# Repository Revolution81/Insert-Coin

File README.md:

<h1 align="center">Insert Coin</h1>

<p align="center">
  <b>A Bitcoin wallet for the M5Stack Cardputer Zero, with a 16-bit arcade look.</b><br>
  Starts with every radio off. Only the signer, in its own locked-down process, ever touches your keys.
</p>

<p align="center">
  <a href="docs/Insert-Coin-Instruction-Booklet.pdf">Instruction booklet (PDF)</a> ·
  <a href="SECURITY.md">Security model</a> ·
  <a href="docs/AUDIT.md">Security review</a> ·
  <a href="CHANGELOG.md">Changelog</a> ·
  <a href="LICENSE">License</a> ·
  <a href="docs/HARDWARE_TEST.md">Hardware test plan</a> ·
  <a href="#donate">Donate</a>
</p>

> [!WARNING]
> Insert Coin is new and **has not had an outside security audit**. The same
> person who wrote it reviewed it. Use testnet or signet first, and keep only
> small amounts on it until it has been reviewed independently.

---

It boots to an animated INSERT COIN title screen (the bitcoin is the O, and
"Running bitcoin..." is a nod to Hal Finney's first tweet about Bitcoin), and
OK plays an original chiptune fanfare. Then it's a full wallet: send, receive,
coin control, multisig, inheritance, tap cards, paper wallets, all on the
Cardputer's own screen and keys.

| | | | |
|:-:|:-:|:-:|:-:|
|  |  |  |  |
| **Home** | **Receive** | **Verify on the signer** | **Confirm send** |
|  |  |  |  |
| **Setup** | **Spending policy** | **Login countdown** | **Print a paper wallet** |

## Features

**Two modes.** Vault mode (the boot default) has Wi-Fi, Bluetooth and
Ethernet (LAN) switched off: sign PSBTs by animated QR or microSD with Sparrow or
any watch-only wallet. Online mode talks to your own Electrum server, through
Tor by default, and sends straight from the device, limited by a daily
online cap.

**Simple by default.** SETUP › DEVICE › ADVANCED (off out of the box) shows the
power-user tools: Co-Sign, temporary seed, child seeds, Key Teleport,
address explorer, paper wallets, watch-only and label exports, QR format,
and the Taproot choice for new multisig. Off, the menus keep to the
everyday things; a tool that's in use stays visible either way.

**Wallet**
- BIP39 seeds (12, 18 or 24 words) or a master xprv. New seeds mix the kernel RNG, the secure chip
  if fitted, and any dice rolls, coin flips, card shuffles or key mashing you add
- Native SegWit (BIP84) and Taproot (BIP86), several accounts per seed, optional passphrase
- Coin control, labels, fee bumps and cancels (RBF), CSV history export
- Pay silent payment addresses (BIP-352) and PayJoin requests (BIP-78)
- Multisig cosigner (BIP48, SegWit or Taproot), inheritance wallets with a time-locked heir key,
  and any miniscript wallet (Liana, Coldcard, Bitcoin Core) with this device's key
- Child seeds and passwords (BIP85), message signing (BIP137, BIP322)
- Temporary seeds and a Seed Vault of extra seeds; an address explorer
- Key Teleport (COLDCARD-compatible): seeds, notes and PSBTs to another device by QR
- Co-Sign: a 2-of-3 where a second key on the device signs only inside its own rules
- QR in every format that matters: PSBT, UR, BBQr, SeedQR
- SATSCARD and TAPSIGNER over NFC (M5Stack's Cap CC1101 & NFC on top, or the NFC Unit on the side port)

**Backups**: seed words, SeedQR, SLIP39 split shares, Seed XOR, and an encrypted card
backup of accounts, multisig wallets, labels, notes, the seed vault and settings
(not your seed itself), with a check that it opens.

**Notes & passwords** kept by the signer, encrypted with the seed.

**Guards**, all on the signer and all changed only with your PIN:
- **Spending policy**: per payment, per day, cooldown, address allow-list, max fee rate
- **Phone 2FA** (TOTP) for every payment or only big ones
- **Bypass PIN** that locks the policy, so your PIN alone can't loosen it or export the seed
- **Login countdown**: a wait of 5 minutes to 24 hours after the right PIN
- **Wipe PIN** (erases everything, device starts like new) and **duress PIN** (opens a decoy wallet)
- **Game PIN**: opens COIN INVADERS, a little space shooter, instead of the wallet, so the
  device looks like a toy (say, at a border). GAME ONLY leaves the wallet locked underneath;
  GAME + WIPE erases everything first. Hold HOME to leave the game
- **Auto lock** after 2 to 15 minutes, a custom time, or never
- Ten wrong PINs erase the wallet; every kind of PIN costs the same time to check

**Extras**: paper wallets kept off the microSD card, printed at home over
encrypted IPP (any AirPrint or IPP Everywhere printer) with a pinned printer certificate, or downloaded with SHARE
FILES (password-protected, local network only, switches itself off), or
SAVE TO USB STICK for your history and PSBTs. Optional
secure chip and fingerprint sensor. One sound switch for the menu boop and
the title fanfare.

## How it's put together

Separate processes, each its own Linux user, so a bug in one doesn't hand
over the others:

| Process | Holds | Network |
|---|---|---|
| **czsigner** | the seed, while unlocked; the screen and keyboard | none |
| **czapp** (the wallet you see) | public keys, history, labels | none |
| **cznet** | nothing | Tor and your Electrum server only |
| **czscan** | nothing; sees the camera | none |
| **czshare** | history exports and paper wallets, while sharing | local network only |
| **czprint** | paper wallets, while printing | local printers only |

The signer doesn't trust the app. It draws its own screens (gold shield in
the corner, your two security words on PIN screens), asks for your PIN and
your YES itself, re-reads every PSBT, re-derives every input and change
output from the seed, needs full previous transactions for SegWit v0 inputs,
checks your spending rules, and signs only the exact PSBT you confirmed.
[SECURITY.md](SECURITY.md) goes through what each process is trusted with
and what's known to be weak.

## Try it on your PC (simulator)

```
pip install -r requirements.txt pygame
python3 sim.py
```

The real app in a window at 3x size. It runs on **signet** (mainnet is off,
because a seed typed into a PC is hot) and simulates Vault/Online without
touching your network settings. Keys follow the Cardputer layout: Enter = OK,
Backspace = DEL, Esc = HOME, F Z X C or the arrow keys move. F12 saves a
screenshot. Data lives in `./simdata`; delete it to start over.

On Windows, put paths with spaces in quotes: `cd "C:\Users\you\Insert Coin"`.

## Install on the Cardputer Zero

Insert Coin comes in two editions. **Pick by how much money it will hold.**

| | **Savings edition** | **Spending edition** |
|---|---|---|
| What it is | A wallet image: the device boots into Insert Coin and runs nothing else | An app in M5Stack's launcher, next to your other apps |
| For | Savings, real amounts | Spending money only, like cash in a pocket |
| Other apps on the device | None | Anything you install from M5Stack's store, which could reach the wallet while it's open |
| How it's labelled | **SAVINGS WALLET** on the title screen, *Savings* in the file name | **SPENDING WALLET** on the title screen, *Insert Coin Spending* in the launcher |

The wallet inside is the same: the signer in its own locked-down process,
Vault mode at every start, your PIN and spending rules. The difference is
what else shares the device. [SECURITY.md](SECURITY.md#app-mode) has the
details.

### Savings edition

**Wallet image (recommended).** Burn
`Insert-Coin-Savings-<version>-cardputerzero.img.xz` from the releases page
with M5 Imager or Raspberry Pi Imager (*Use custom*), after checking its
SHA-256. It's M5Stack's CardputerZero OS with Insert Coin installed in
dedicated mode by `tools/build_image.sh`, built in public by the *Build
wallet image* workflow, so anyone can see what went in. It fits an 8 GB card
or bigger. It takes **no logins at all**: SSH is off and every account's
password is locked, so the screen and keyboard are the only way in. Browsers,
media players and remote-desktop servers are removed from it.

**Updating.** Releases that only change the wallet come as two files,
`Insert-Coin-Update-<version>.tar.gz` and its `.sig`. Put the card in a PC,
copy both into a folder named `Insert-Coin-Update` on its boot partition (or
onto a USB stick), put the card back and open SETUP › UPDATE. The wallet checks the
signature against the release key built into the image, shows the version
and SHA-256, and installs; the previous version is kept. Releases that need a
newer M5Stack OS come as a new image instead: have your seed words, copy the
card's `czwallet-backup` folder off first, burn, restore from words, and the
wallet offers to bring back your accounts and settings.

*If the image won't start:* put the card in a PC, create an empty file named
`insert-coin-debug.txt` on its boot partition (the part Windows can read),
put it back and power on for 10 minutes. The device then writes its startup
log to `insert-coin-bootlog.txt` on the same partition. Delete both files
afterwards: the log can name your Wi-Fi network.

**Or on the card you already have:** `sudo sh deploy/install.sh --dedicated`,
then `sudo reboot`. `sudo sh deploy/uninstall.sh` brings the launcher back.

### Spending edition

Keeps the CardputerZero home screen; **Insert Coin Spending** gets an icon
there. Over SSH:
```
sudo apt-get install -y git
git clone https://github.com/Revolution81/Insert-Coin.git
cd Insert-Coin && sudo sh deploy/install.sh --app
```
Opening the icon starts the wallet in Vault mode; SETUP › EXIT TO MENU locks
it, stops every wallet service and puts Wi-Fi back as it was.
To update: `cd ~/Insert-Coin && git pull && sudo sh deploy/install.sh --app`
(quick after the first time: steps already done are skipped).
`sudo sh deploy/uninstall.sh` removes it. Keep only spending money on it.

The installer creates the service users, installs the code under
`/opt/czwallet-releases/<version>` with a Python venv, the data folders, the
root helpers (radios on/off, signed updates, backups), a polkit rule for
Wi-Fi, and Tor. Dependencies are pinned with SHA-256 hashes in
`requirements.lock`.

Things to check on a device (keys, screen, network, camera) are in
[docs/HARDWARE_TEST.md](docs/HARDWARE_TEST.md). Try **signet** first: choose
NETWORK on the welcome screen.

## Keys

Menus: **F Z X C** move (the arrows printed on F▲ Z◀ X▼ C▶), **OK** select,
**DEL** back, the **HOME** button home.
Home screen: **S** send, **R** receive, **H** history, **M** mode, **Q** scan
anything, **T** tap a card, **W** wallets, **L** lock.
Receive: **N** new address, **L** label, **V** verify on the signer, **M** sign a message.
Typing: every key types, **fn + F Z X C** moves the cursor, **OK** done, **HOME** cancel.

## Develop

```
pip install -r requirements.txt pytest
python3 -m pytest tests                     # 480 tests, offline
python3 tools/fuzz.py                       # junk input at every parser
python3 tools/monkey.py 10 1500             # random key-mashing robot
python3 tools/leakcheck.py                  # long-running memory loops
python3 tools/shots.py shots/               # screenshots of the real app
```

<details>
<summary>Source layout</summary>

```
app.py                 the app: menus, camera, watch-only wallet
sim.py                 desktop simulator (pygame)
core/
  signer.py            the only code with private keys; checks every PSBT
  signer_service.py    runs the signer as its own user; owns screen and keyboard
  trusted.py           what the app may ask the signer (no PIN or seed ever crosses)
  vault.py             seed encrypted at rest: Argon2id + AES-GCM, PIN tries, wipe
  policy.py            spending policy, TOTP 2FA, bypass PIN
  seed.py              BIP39 seeds and entropy mixing; BIP84 keys
  accounts.py          wpkh:N (BIP84) and tr:N (BIP86) accounts
  wallet.py            watch-only wallet: coins, history, build PSBT, broadcast
  electrum.py, netd.py Electrum client (TLS, Tor) and the cznet relay
  scand.py             czscan: camera + QR decoding, sandboxed
  qr.py, ur.py         what a QR means; UR codes
  multisig.py, inherit.py, split.py, bip85.py, message.py, backup.py
  cktap.py, hw/        SATSCARD/TAPSIGNER, NFC, secure chip, fingerprint
  paper.py, printing.py, ipp.py, mdns.py   paper wallets and printing
  share.py             SHARE FILES web server
  update.py            reproducible release builds, signatures, safe install
ui/                    screens, theme, title, sound, and the signer's own screens
deploy/                systemd units, root helpers, install.sh
tools/                 tests on hardware, releases, fuzzer, monkey, screenshots
tests/                 python3 -m pytest tests
```
</details>

## Security notes, honestly

- **No outside audit yet.** Read [SECURITY.md](SECURITY.md) and
  [docs/AUDIT.md](docs/AUDIT.md) for the threat model, the internal review
  and the known gaps.
- Without the optional secure chip, someone who copies the microSD card can
  try PINs offline against the vault file, slowed only by Argon2 (64 MiB,
  about 1 to 2 s per guess on the CM0). A 6-digit PIN would fall in days that
  way. Use a longer PIN or a passphrase you don't store, or fit the chip.
- Online mode makes it a hot wallet. The online cap and your spending rules
  limit the damage.
- SD cards remap blocks, so wiping can't promise every old copy is gone.
  Treat a lost card as exposed to the offline attack above.
- Keep real savings on the savings edition, in Vault mode, or in a multisig
  where this device is one key. The spending edition is for spending money.

## Donate

Insert Coin is free and made by one person. If it's useful to you, a
donation helps pay for the work, test devices and an outside security audit.
Bitcoin only, on-chain:

```
bc1qca69hxsnkwtqn7j9wmjeyg5tutwx38rdwfzx8k
```

## License

**Source-available, not open source.** Anyone may read, audit, build and run
Insert Coin, including paid security reviews, under the
[PolyForm Strict License 1.0.0](LICENSE) plus the extra permissions at the top
of that file. Publishing or distributing it, changed or not, needs written
permission. Third-party libraries and fonts keep their own licenses: see
[THIRD_PARTY_NOTICES.md](THIRD_PARTY_NOTICES.md).

Found a security problem? Please report it privately: see
[SECURITY.md](SECURITY.md#reporting).

Insert Coin is an independent project, not affiliated with or endorsed by
M5Stack. Cardputer Zero is a product of M5Stack. Bitcoin only.

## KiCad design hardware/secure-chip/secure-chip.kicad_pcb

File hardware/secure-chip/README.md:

# Secure chip board (v1, untested)

A 24 x 16 mm board that plugs onto the Cardputer Zero's **EXT 2x7 header**
and gives Insert Coin a **blank ATECC608B** secure chip, for the mode where
the chip itself counts wrong PINs.

**Status: designed, not yet built.** Prove the same circuit on a breadboard
first (Adafruit 4314 breakout + MCP1700 + two 1 µF capacitors + two 4.7 kΩ
pull-ups to 3.3 V + male-to-male jumper wires), then order.

## Breadboard test first

`breadboard-test.svg` / `.png`, made by `gen_breadboard.py`.

## Circuit

- EXT pin 6 (**5V OUT**) -> MCP1700T-3302E/TT -> **3.3 V** for the chip.
  1 µF in, 1 µF out, 100 nF at the chip.
- EXT pin 3 (**G23 SDA**) and pin 1 (**G26 SCL**) to the chip, with 4.7 kΩ
  pull-ups to 3.3 V. That's a **bus of its own** (I2C bus 3, software I2C
  on GPIO23/26). From 0.8.42 the wallet makes that bus by itself while
  running, when no Cap answers on the header: nothing to set, no restart.
  (0.8.41's EXT HEADER setting never took effect: the root helper only
  received the word "extbus".)
- EXT pin 4 GND. **Pin 2 (5V IN) is not connected**: it powers the device.
- The chip answers at **0x60**, alone on its bus.

**Why not pins 8 and 10 (I2C1), as v1 first had it:** that bus carries the
keyboard (0x34), battery gauge (0x55), audio codec (0x10), the IO expander
(0x4F) and the RTC. The chip's power on pin 6 only comes on once the wallet
starts, and until then the unpowered chip and its pull-ups held those wires
down: the keyboard and the IO expander never started, and the IO expander
restarted the Cardputer in a loop (M5 logo, black, M5 logo...). Seen on the
device, 2026-11-26. On its own bus an unpowered or miswired chip can't stop
anything from starting. **The board drawing below still routes SDA/SCL to
pins 8 and 10 and needs the same change before it's ordered.**

From M5Stack's schematic (V0.6.1): 5V OUT goes through a load switch
enabled by the IO expander's **HAT_EN** line. M5Stack's system keeps it off
(the "LED" `ext_5v_out`, default off); Insert Coin 0.8.31 and later switch
it on at start and on RESCAN (confirmed on the device with the NFC Cap).
Check with a meter on the breadboard first anyway.

The NFC Cap uses the same EXT header, so it's one or the other: take the
Cap off (device powered off) for this board.

## Building it

- Parts on the **front** (outside). The **2x7 male header goes on the back**,
  plastic body against the board, long pins pointing at the Cardputer,
  soldered on the front.
- Seen from the front, the pin rows match the label on the Cardputer: odd
  pins (G26 ... G7) on the row nearest the keyboard (`^ KEYS`), even pins
  (5V IN, GND, 5V OUT, SDA, SCL, ...) below.
- **Power the Cardputer off before plugging it in or out.** The port isn't
  hot-swappable.
- Check the fit against the microSD slot to the right of the header before
  ordering. The board extends 1.3 mm past the header's right-hand pins.

## Files

| File | What |
|---|---|
| `secure-chip.kicad_sch`, `.kicad_pcb`, `.kicad_pro` | KiCad 7 project |
| `secure-chip-schematic.pdf` | the schematic |
| `secure-chip-assembly.png` | where each part goes, which way round, and what each header pin is |
| `fab/secure-chip-gerbers.zip` | upload to JLCPCB / PCBWay (2 layers, 1.6 mm) |
| `fab/secure-chip-bom.csv`, `fab/secure-chip-cpl.csv` | parts list and placement, for assembly |
| `gen_sch.py`, `gen_pcb.py`, `make_fab.sh` | the design is generated by these; `make_fab.sh` rebuilds and re-checks everything |
| `check_net.py`, `check_pcb.py`, `drc.rpt` | netlist and copper checked against the intended connections; KiCad DRC: 0 violations |

Part of Insert Coin; same license as the rest of the repository.

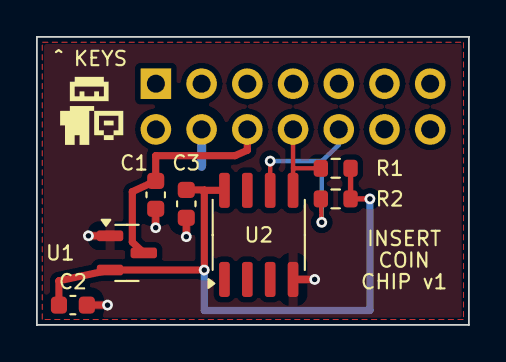
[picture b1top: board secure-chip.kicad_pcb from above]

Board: 2 copper layers, 24.0 x 16.0 mm, 8 parts (1 on the bottom side), 5 nets.

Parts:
C1, C2: 1uF; C_0603_1608Metric
C3: 100nF; C_0603_1608Metric
J1: EXT 2x7; PinHeader_2x07_P2.54mm_Vertical
R1, R2: 4.7k; R_0603_1608Metric
U1: MCP1700T-3302E/TT; SOT-23
U2: ATECC608B-SSHDA; SOIC-8_3.9x4.9mm_P1.27mm

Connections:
+3V3: C2.1, C3.1, R1.1, R2.1, U1.2, U2.8
+5V: C1.1, J1.6, U1.3
GND: C1.2, C2.2, C3.2, J1.4, U1.1, U2.4
SCL: J1.10, R2.2, U2.6
SDA: J1.8, R1.2, U2.5
